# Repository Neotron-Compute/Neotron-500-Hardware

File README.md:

# Neotron 500

> A Neotron based home computer, powered by an 32-bit ARM Cortex-M7, with USB 2.0 and hardware accelerated VGA graphics.

## The top-level Specs

* 480 MHz 32-bit ARM Cortex-M7 CPU core
* 1024 KiB of fast internal ECC SRAM (used as VRAM and for OS buffers)
* 8 MiB slow external 16-bit 120 MHz SDRAM
* Super-VGA output
   * 720x400 @ 70 Hz (80x25 VGA text mode)
   * 640x480 @ 60 Hz (VGA graphics mode)
   * 800x600 @ 60 Hz (SVGA graphics mode)
   * 256 colours from a pallette of 262,144 (via 18-bit 6/6/6 DAC)
* 16-bit 48 kHz audio input and output (line-in, mic-in, line-out and headphone-out)
* Four high-speed (480 Mbps) USB 2.0 ports
   * Two USB A ports on-board
   * Header for additional two ports
* RS232 Port (five-wire)
* 2x SD/MMC Slots
* PS/2 Keyboard and Mouse ports
* Battery-backed Real-time Clock and CMOS RAM
* SPI and I²C based expansion bus

## Why 500?

We already had a Neotron 32 and a Neotron 1000, and this was somewhere inbetween the two. Plus it's roughly the performance of an Amiga 500.

## The detailed specs

### The Processor

The Neotron-500 uses an [STM32H743IIT6] microcontroller.

[STM32H743IIT6]: https://www.st.com/en/microcontrollers-microprocessors/stm32h743ii.html

```
STM32H743IIT6
vvvvv||vv|||+-- -40°C to +85°C
  |  ||| ||+-- LQFP Package
  |  ||| |+-- 2048 KiB Flash
  |  ||| +-- 176 pin
  |  ||+-- USB OTG FS/HS, Ethernet, LCD-TFT
  |  |+-- Cortex-M7
  |  +-- High-performance family
  +-- 32-bit ARM Microcontroller from ST Micro
```

This microcontroller has:

* An ARM Cortex-M7F core
  * dual-issue, six-stage pipeline
  * hardware floating point
  * 16 KiB instruction cache
  * 16 KiB data cache  
* Clockspeed of up to 480 MHz
* 176 pins, in a low-profile quad flat package (LQFP)
* 2 MiB Flash
* 128 KiB tightly-coupled (Cortex-M only) data SRAM
* 64 KiB tightly-coupled (Cortex-M only) instruction SRAM
* 512 KiB of AXI-SRAM with ECC
* Further ECC SRAM banks of 128, 128, 64 and 32 KiB each
* 4 KiB of battery-backed SRAM
* External parallel memory bus interface with SDRAM support
* Memory-mapped 133 MHz Quad-SPI interface (QSPI Flash only, not RAM)
* MII/RMII 10/100 Ethernet MAC
* USB Full-speed (12 Mbps) OTG MAC/PHY
* USB High-speed (480 Mbps) OTG MAC
* 24-bit LCD-TFT interface with ChromART 2D video accelerator
* Hardware JPEG, random number generator and CRC
* RTC with 4 KiB battery backed RAM
* MIPI CSI Camera interface
* 2x SD/MMC controllers
* Multiple I²S interfaces
* Multiple UART interfaces
* Multiple SPI bus interfaces
* Multiple I²C bus interfaces
* Multiple CAN bus interfaces

In terms of the CoreMark benchmark (and when running from internal Flash), this CPU is about the same speed as a Raspberry Pi Zero (despite running at just 40% of the clock speed), and somewhere around an 866 MHz Pentium III with 64-bit SDRAM. We run from external 16-bit SDRAM, however, and that is where we are down on performance. PC66 SDRAM is 64-bits wide and has a peak bandwidth of around 500 MiB/sec. Our 16-bit 120 MHz SDRAM meanwhile is more like 228 MiB/sec. But I'm hoping it will still run Doom.

### Memory Layout

We expect to use:

* 128 KiB tightly-coupled data SRAM for the system stack and OS data.
* 64 KiB tightly-coupled instruction SRAM for OS routines.
* 128 KiB SRAM for DMA and device buffers.
* 512 KiB AXI-SRAM for video frame buffers.
  * Highest resolution 800x600 mode @ 8bpp = 468 KiB
* (Remaining 128 KiB and 64 KiB banks TBD)
* 4 KiB battery backed SRAM for system settings
* 512 KiB internal Flash for the Neotron BIOS
* 512 KiB internal Flash for Neotron OS
* 1024 KiB internal Flash for ROM-based user applications
* 8192 KiB external SDRAM for RAM-based user applications

## The Motherboard

The Neotron 500 Motherboard is completely open-source hardware, and all the components are either through-hole parts that are easy to self install, or available from the [JLCPCB SMT assembly service].

The motherboard has:

* Regulated 5V Input
  * If you want to power four 500 mA USB devices from your Neotron 500, this needs to be capable at least 2.5A
  * TBD whether this is a DC barrel jack, full-size USB B, mini USB B or micro USB B
  * Or even take 5V from a 110V/240V internal PSU
  * Or we could take 7V-15V from a DC barrel jack and have an on-board 5V DC-DC regulator, like the Raspberry Pi CM4 IO Board
* TPS5430 3.3V 3A DC/DC Convertor (currently using an AMS1117-3.3 1A LDO)
* Winbond W9864G6KH-6 4Mx16 SDRAM
  * 8192 KiB capacity
  * 16-bit interface
  * Up to 200 MHz clock rate (we run at 120 MHz)
* Texas Instruments TLV320AIC23BPW Audio Codec ($2.32)
  * 16-bit 44.1/22.05/11.025 kHz I²S input and output to the STM32
  * Amplified stereo 3.5mm TRS headphone output
  * Line-level stereo 3.5mm TRS output
  * Line-level stereo 3.5mm TRS input
  * Mono microphone 3.5mm input
* Microchip USB3300 High-speed (480 Mbps) ULPI USB 2.0 PHY ($1.52)
* Microchip USB2514B High-speed (480 Mbps) four port USB 2.0 hub, with 2x2 USB 2.0 A ports. ($1.43)
* 18-bit (6-6-6) R2R DAC and 3PEAK TPF133A HD video output buffer ($0.16), with standard DE15HD VGA connector.
* Maybe a TPD7S019 ESD protection device / SYNC buffer for the VGA connector ($0.26)
* Full-size external-facing SD Card slot (drive A:)
* Full-size internal SD Card slot (drive C:)
* Maxim MAX16054 on-off controller ($1.11)
* Keyboard / Mouse interface
  * 2x PS/2 Ports for keyboard and mouse (2x mini-DIN 6-pin sockets)
* Power switch and reset switch
* RS232 Port (five-wire, 10-pin IDC box header as used on PCs)
* Coin-cell for the STM32's real-time clock and battery-backed SRAM
* SPI/QSPI and I²C based expansion bus
  * There are seven slots
  * Each slot has a unique SPI Chip-select and IRQ line
  * Each slot contains a unique 3-bit value, which is routed to the 3 address pins of an M24C02 256 byte I²C EEPROM on the expansion card
  * The I²C EEPROM describes that expansion card (similar to the Raspberry Pi HAT specification, but supporting multiple slots)

[JLCPCB SMT assembly service]: https://jlcpcb.com/parts

Expected price is $40 for the motherboard with SMT parts loaded, and another $20 for the through-hole connectors. The system does not include a Parallel Port, Ethernet, Joystick ports, Keyboard matrix controller, MIDI ports or Wi-Fi - modules can be added via the SPI expansion ports for these features. Although the STM32F7 does have an on-board Ethernet MAC, we cannot use it and all the other interfaces (SDRAM, SDMMC, ULPI, LCD) at the same time.

## Software

This system is designed to run the Neotron OS. To do that, it has a bespoke version of the Neotron BIOS. It is compatible with all 'well-behaved' Neotron applications that stick to the Neotron OS APIs rather than poking hardware directly.

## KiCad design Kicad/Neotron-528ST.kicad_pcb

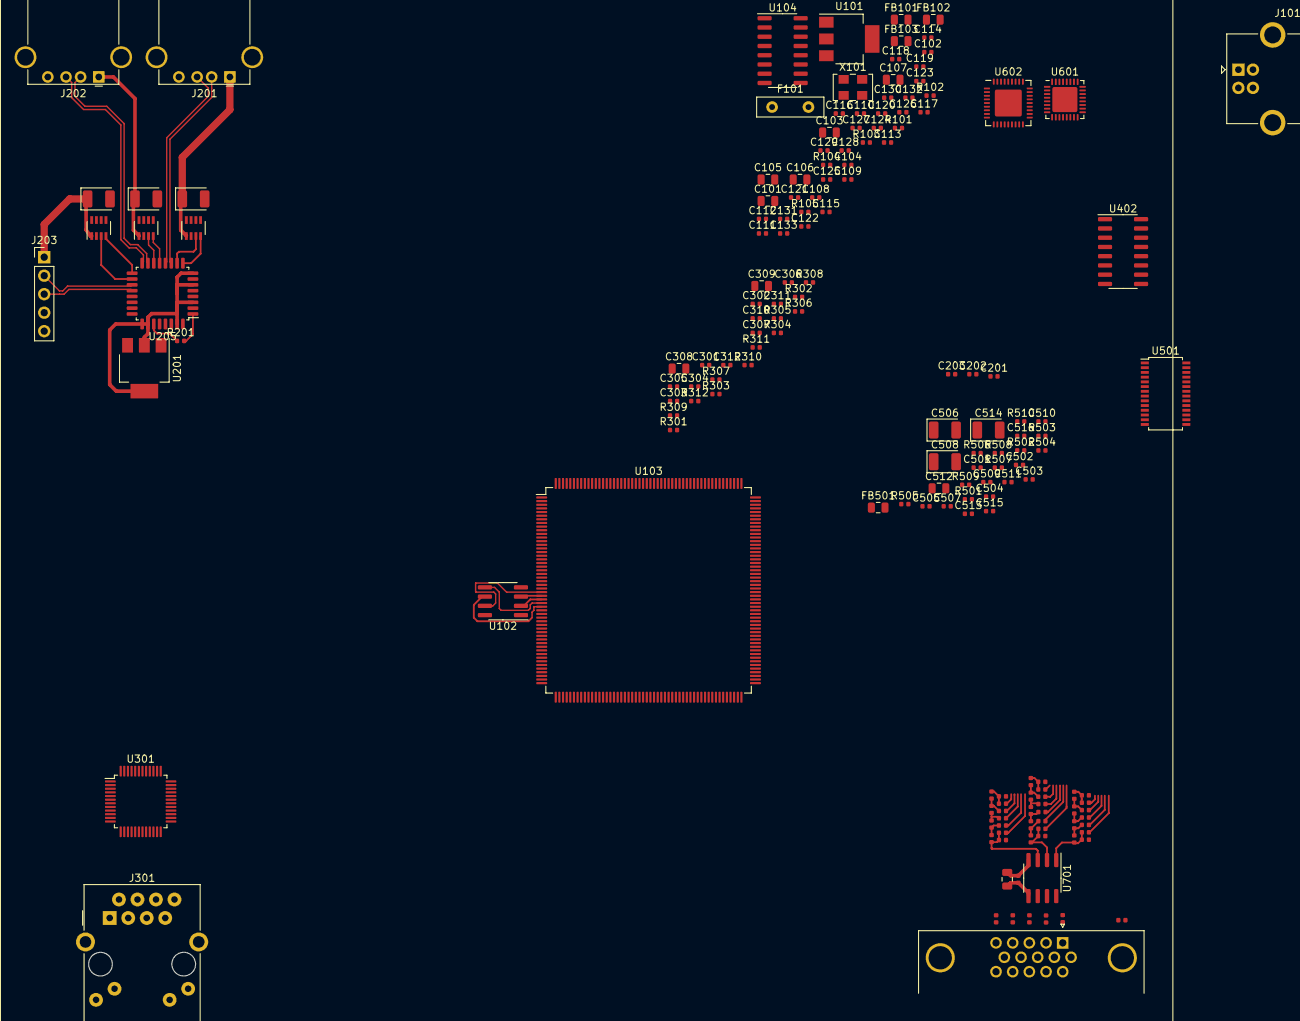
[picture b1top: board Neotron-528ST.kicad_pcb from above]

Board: 2 copper layers, 165 parts (0 on the bottom side), 125 nets.

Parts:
C101, C103, C105: 22u; C_0805_2012Metric
C102, C104, C108, C113, C115, C117, C119, C120, C121, C122, C123, C124, C125, C126, C128, C129, C130, C131, C132, C133, C201, C301, C302, C303, C304, C305, C306, C307, C310, C311, C312, C511, C513, C702: 100n; C_0402_1005Metric
C106, C107: 2.2u; C_0805_2012Metric
C109, C110, C111, C112: 9p; C_0402_1005Metric
C114, C116, C118, C127, C501, C502, C504, C505, C509: 1u; C_0402_1005Metric
C202, C203: 4.7u; C_0402_1005Metric
C204, C205, C206, C506, C508, C514: 100u; CP_EIA-3528-21_Kemet-B
C308, C309, C512: 10u; C_0805_2012Metric
C503, C507, C510: 47p; C_0402_1005Metric
C515, C516: 27p; C_0402_1005Metric
C701: 4.7u; C_0805_2012Metric
F101: 2.5A; C_Disc_D9.0mm_W2.5mm_P5.00mm
FB101, FB102, FB103, FB501: 100R@100MHz; L_0805_2012Metric
J101: USB_B; USB_B_OST_USB-B1HSxx_Horizontal
J201, J202: USB_A; USB_A_Stewart_SS-52100-001_Horizontal
J203: USB_A; PinHeader_1x05_P2.54mm_Vertical
J301: RJ45_Amphenol_RJMG1BD3B8K1ANR
J701: DB15_Female_HighDensity_MountingHoles; DSUB-15-HD_Female_Horizontal_P2.29x1.98mm_EdgePinOffset3.03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
R101, R102, R103, R312: 0R; R_0402_1005Metric
R104, R105: 10k; R_0402_1005Metric
R201: 1.5k; R_0402_1005Metric
R301, R302, R305, R307: 49.9R; R_0402_1005Metric
R303, R304, R306, R310: 2k2; R_0402_1005Metric
R308, R309: 1k; R_0402_1005Metric
R311: 4.87K; R_0402_1005Metric
R501: 2.2k; R_0402_1005Metric
R502, R503, R506, R507: 100k; R_0402_1005Metric
R504, R508: 4.99k; R_0402_1005Metric
R505, R509: 5k; R_0402_1005Metric
R510: 3R3; R_0402_1005Metric
R701, R702, R703, R704, R705, R711, R717, R718, R719, R720, R721, R722, R729, R731, R732, R733, R734, R735, R740: 24K; R_0402_1005Metric
R706, R707, R708, R709, R724, R725, R726, R727, R728, R736, R737, R738, R739: 12K; R_0402_1005Metric
R710, R730, R741: 3K3; R_0402_1005Metric
R712, R713, R714: 75; R_0402_1005Metric
R715, R716: 470; R_0402_1005Metric
R723: 0; R_0402_1005Metric
U101, U201: AMS1117-3.3; SOT-223-3_TabPin2
U102: LY68S3200SLT; SOIC-8_3.9x4.9mm_P1.27mm
U103: STM32F767BGTx; LQFP-208_28x28mm_P0.5mm
U104: MAX232; SOIC-16_3.9x9.9mm_P1.27mm
U202, U203, U204: AAT4610BIGV-1-T1; SOT-23-8
U205: TUSB2036; LQFP-32_7x7mm_P0.8mm
U301: DP83848C; LQFP-48_7x7mm_P0.5mm
U402: 74LS138; SOIC-16_3.9x9.9mm_P1.27mm
U501: TLV320AIC23BPW; TSSOP-28_4.4x9.7mm_P0.65mm
U601: USB3300-EZK; QFN-32-1EP_5x5mm_P0.5mm_EP3.45x3.45mm
U602: USB2514B_Bi; QFN-36-1EP_6x6mm_P0.5mm_EP3.7x3.7mm
U701: TPF133A; SOIC-8_3.9x4.9mm_P1.27mm
X101: 50MHz XO; Oscillator_SMD_TXC_7C-4Pin_5.0x3.2mm

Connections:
+3V3: C108.1, C301.1, C302.1, C303.1, C304.1, C511.1, C512.1, C701.1, C702.1, FB501.1, J301.R4, J301.R5, R301.2, R302.1, R305.2, R306.1, R307.1, R308.2, R309.2, R310.1, R312.2, U102.8, U301.22, U301.32, U301.48, U501.1, U501.22, U501.27, U701.4, X101.1, X101.4
+5V: C101.1, C104.1, C105.1, C201.1, C202.1, F101.1, U101.3, U201.3, U202.5, U203.5, U204.5
/Audio/HEADPHONE_L: C506.1, U501.9
/Audio/HEADPHONE_R: C508.1, U501.10
/Audio/LINE_IN_L: C505.1, U501.20
/Audio/LINE_IN_R: C509.1, U501.19
/Audio/LINE_OUT_L: C502.1, U501.12
/Audio/LINE_OUT_R: C504.1, U501.13
/Audio/MIC_IN: C501.1, U501.18
/Audio/VDD_AUDIO: C513.1, C514.1, FB501.2, R510.2, U501.8
/Audio/V_MICBIAS: R501.1, U501.17
/Ethernet PHY/LED_ACT: J301.L2, U301.26
/Ethernet PHY/LED_SPEED: J301.L3, U301.27
/LTDC_B3: R731.1, U103.110
/LTDC_B4: R732.1, U103.144
/LTDC_B5: R733.1, U103.187
/LTDC_B6: R734.1, U103.188
/LTDC_B7: R735.1, U103.189
/LTDC_G2: R717.1, U103.55
/LTDC_G3: R718.1, U103.85
/LTDC_G4: R719.1, U103.123
/LTDC_G5: R720.1, U103.126
/LTDC_G6: R721.1, U103.127
/LTDC_G7: R722.1, U103.128
/LTDC_HSYNC: R715.2, U103.12
/LTDC_R3: R701.1, U103.67
/LTDC_R4: R702.1, U103.68
/LTDC_R5: R703.1, U103.69
/LTDC_R6: R704.1, U103.95
/LTDC_R7: R705.1, U103.65
/LTDC_VSYNC: R716.2, U103.11
/QUADSPI_BK1_IO0: U102.2, U103.29
/QUADSPI_BK1_IO1: U102.5, U103.30
/QUADSPI_BK1_IO2: U102.3, U103.28
/QUADSPI_BK1_IO3: U102.7, U103.27
/QUADSPI_BK1_NCS: U102.1, U103.195
/QUADSPI_CLK: U102.6, U103.31
/RCC_OSC32_IN: C111.1, U103.9
/RCC_OSC32_OUT: C112.1, U103.10
/RCC_OSC_IN: C109.1, U103.32
/RCC_OSC_OUT: C110.1, U103.33
/USB 1.1 Host/HUB_3V3: C203.1, U201.2, U205.3, U205.6, U205.8, U205.25, U205.26, U205.31
/USB 1.1 Host/PORT1_D+: J201.3, U205.12
/USB 1.1 Host/PORT1_D-: J201.2, U205.11
/USB 1.1 Host/PORT2_D+: J202.3, U205.16
/USB 1.1 Host/PORT2_D-: J202.2, U205.15
/USB 1.1 Host/PORT3_D+: J203.3, U205.20
/USB 1.1 Host/PORT3_D-: J203.2, U205.19
/USB 1.1 Host/~PORT1_EN: U202.4, U205.9
/USB 1.1 Host/~PORT1_OC: U202.3, U205.10
/USB 1.1 Host/~PORT2_EN: U203.4, U205.13
/USB 1.1 Host/~PORT2_OC: U203.3, U205.14
/USB 1.1 Host/~PORT3_EN: U204.4, U205.17
/USB 1.1 Host/~PORT3_OC: U204.3, U205.18
/USB_OTG_HS_D+: R201.2, U205.1
/VDDA: C115.1, C116.1, FB101.2, R101.2, U103.42
/VDD_MCU: C102.1, C103.1, C119.1, C120.1, C121.1, C122.1, C123.1, C124.1, C125.1, C128.1, C129.1, C130.1, C131.1, C132.1, C133.1, FB101.1, R102.2, R103.2, U101.2, U103.15, U103.26, U103.39, U103.52, U103.59, U103.73, U103.83, U103.94, U103.103, U103.115, U103.124, U103.150, U103.158, U103.185, U103.204
/VDD_SDMMC: C126.1, C127.1, R102.1, U103.171
/VDD_USB: C117.1, C118.1, R103.1, U103.137
/VGA Video Output/ANALOG_BLUE: R735.2, R739.1, R741.1, U701.3
/VGA Video Output/ANALOG_GREEN: R722.2, R728.1, R730.1, U701.2
/VGA Video Output/ANALOG_RED: R705.2, R709.1, R710.1, U701.1
/VGA Video Output/BOUT: R714.1, U701.6
/VGA Video Output/GOUT: R713.1, U701.7
/VGA Video Output/ROUT: R712.1, U701.8
/VREF+: C113.1, C114.1, R101.1, U103.41
GND: C101.2, C102.2, C103.2, C104.2, C105.2, C106.2, C107.2, C108.2, C109.2, C110.2, C111.2, C112.2, C113.2, C114.2, C115.2, C116.2, C117.2, C118.2, C119.2, C120.2, C121.2, C122.2, C123.2, C124.2, C125.2, C126.2, C127.2, C128.2, C129.2, C130.2, C131.2, C132.2, C133.2, C201.2, C202.2, C203.2, C204.2, C205.2, C206.2, C301.2, C302.2, C303.2, C304.2, C305.2, C306.2, C307.2, C308.2, C309.2, C310.2, C311.2, C312.2, C511.2, C512.2, C513.2, C514.2, C515.2, C516.2, C701.2, C702.2, FB103.1, J101.4, J201.4, J201.5, J202.4, J202.5, J203.4, J203.5, J301.13, J301.R8, J701.5, J701.6, J701.7, J701.8, R104.2, R303.2, R304.2, R311.1, R710.2, R711.2, R723.2, R729.2, R730.2, R740.2, R741.2, U101.1, U102.4, U103.14, U103.25, U103.40, U103.51, U103.60, U103.72, U103.82, U103.93, U103.114, U103.125, U103.136, U103.149, U103.170, U103.184, U103.202, U201.1, U202.2, U203.2, U204.2, U205.7, U205.21, U205.22, U205.23, U205.24, U205.28, U301.15, U301.19, U301.35, U301.36, U301.47, U501.28, U701.5, X101.2
GNDA: C503.2, C507.2, C510.2, R502.1, R503.1, R505.1, R506.1, R507.1, R509.1, U501.11, U501.15
unnamed: C106.1, U103.92
unnamed: C107.1, U103.148
unnamed: C204.1, J201.1, U202.1
unnamed: C205.1, J202.1, U203.1
unnamed: C206.1, J203.1, U204.1
unnamed: C305.1, U301.37
unnamed: C306.1, U301.18
unnamed: C307.1, C308.1, U301.23
unnamed: C309.1, C310.1, C311.1, C312.1, R312.1
unnamed: C501.2, C503.1, R501.2
unnamed: C502.2, R502.2
unnamed: C504.2, R503.2
unnamed: C505.2, C507.1, R504.1, R505.2
unnamed: C506.2, R506.2
unnamed: C508.2, R507.2
unnamed: C509.2, C510.1, R508.1, R509.2
unnamed: C515.1, U501.25
unnamed: C516.1, U501.26
unnamed: F101.2, FB102.2
unnamed: FB102.1, J101.1
unnamed: FB103.2, J101.5
unnamed: J301.L1, R309.1
unnamed: J301.L4, R308.1
unnamed: J301.R1, R301.1, U301.17
unnamed: J301.R2, R302.2, U301.16
unnamed: J301.R3, R305.1, U301.14
unnamed: J301.R6, R307.2, U301.13
unnamed: J701.0, R723.1
unnamed: J701.1, R712.2
unnamed: J701.2, R713.2
unnamed: J701.3, R714.2
unnamed: J701.13, R715.1
unnamed: J701.14, R716.1
unnamed: R104.1, U103.203
unnamed: R105.1, U103.197
unnamed: R201.1, U205.27
unnamed: R303.1, U301.5
unnamed: R304.1, U301.6
unnamed: R306.2, U301.39
unnamed: R310.2, U301.7
unnamed: R311.2, U301.24
unnamed: R510.1, U501.14
unnamed: R701.2, R706.2, R711.1
unnamed: R702.2, R706.1, R707.2
unnamed: R703.2, R707.1, R708.2
unnamed: R704.2, R708.1, R709.2
unnamed: R717.2, R724.2, R729.1
unnamed: R718.2, R724.1, R725.2
unnamed: R719.2, R725.1, R726.2
unnamed: R720.2, R726.1, R727.2
unnamed: R721.2, R727.1, R728.2
unnamed: R731.2, R736.2, R740.1
unnamed: R732.2, R736.1, R737.2
unnamed: R733.2, R737.1, R738.2
unnamed: R734.2, R738.1, R739.2
unnamed: U601.7, U602.31
unnamed: U601.8, U602.30

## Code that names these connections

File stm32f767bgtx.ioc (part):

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PK5.Signal=LTDC_B6
PH12.Signal=I2C4_SDA
PB10.Mode=Host_HS
PK0.Mode=RGB565
PG4.Signal=FMC_A14_BA0
PC12.Signal=SDMMC1_CK
PG0.Signal=FMC_A10
PC5.Mode=MII
PK1.Signal=LTDC_G6
PB13.Signal=USB_OTG_HS_ULPI_D6
PG13.Signal=ETH_TXD0
PA4.Mode=Half_Duplex_Slave
PF7.Signal=QUADSPI_BK1_IO2
PJ5.Mode=RGB565
PD4.Signal=FMC_NOE
PB6.Signal=QUADSPI_BK1_NCS
PC7.Signal=FMC_NE1
PH1/OSC_OUT.Signal=RCC_OSC_OUT
PB6.Mode=Single Bank 1
PC3.Signal=ETH_TX_CLK
PD0.Signal=FMC_D2_DA2
PD8.Signal=USART3_TX
PE5.Signal=FMC_A21
PI3.Mode=Half_Duplex_Master
PB2.Signal=I2S3_SD
PB3.Mode=Half_Duplex_Slave
PG14.Mode=MII
PK7.Mode=RGB565
PJ2.Mode=RGB565
PE9.Signal=FMC_D6_DA6
PB14.Mode=CTS_RTS
PI3.Signal=I2S2_SD
PC9.Mode=SD_4_bits_Wide_bus
PE2.Signal=FMC_A23
PF8.Mode=Single Bank 1
PA8.Signal=RCC_MCO_1
PE13.Mode=Full_Duplex_Master
PF3.Signal=FMC_A3
PE10.Signal=FMC_D7_DA7
Mcu.Package=LQFP208
PB1.Signal=USB_OTG_HS_ULPI_D2
PH12.Mode=I2C
PD12.Signal=FMC_A17_ALE
PH11.Mode=I2C
PJ4.Signal=LTDC_R5
PA10.Signal=LTDC_B4
PC11.Mode=SD_4_bits_Wide_bus
PF14.Signal=FMC_A8
PF10.Mode=Single Bank 1
PB13.Mode=Host_HS
PI11.Signal=USB_OTG_HS_ULPI_DIR
PD15.Signal=FMC_D1_DA1
PC4.Mode=MII
PA5.Mode=Host_HS
PE12.Mode=Full_Duplex_Master
PK4.Signal=LTDC_B5
PG5.Signal=FMC_A15_BA1
PI10.Mode=RGB565
PC6.Signal=I2S2_MCK
PC2.Signal=ETH_TXD2
PD1.Signal=FMC_D3_DA3
PC0.Signal=USB_OTG_HS_ULPI_STP
PJ11.Signal=LTDC_G4
PD10.Signal=LTDC_B3
PA3.Mode=Host_HS
PJ3.Signal=LTDC_R4
PB11.Mode=Host_HS
PC6.Mode=Master_Clock_Activated
PA9.Signal=I2S2_CK
PD8.Mode=Asynchronous
PA0/WKUP.Mode=MII
PB10.Signal=USB_OTG_HS_ULPI_D3
PB14.Signal=UART4_RTS
PA5.Signal=USB_OTG_HS_ULPI_CK
PC12.Mode=SD_4_bits_Wide_bus
PH6.Mode=MII
PA1.Mode=MII
PE14.Signal=SPI4_MOSI
PE8.Signal=FMC_D5_DA5
PF13.Signal=FMC_A7
PH4.Mode=Host_HS
PC8.Mode=SD_4_bits_Wide_bus
PA4.Signal=I2S3_WS
PB5.Signal=USB_OTG_HS_ULPI_D7
PK4.Mode=RGB565
PD11.Signal=FMC_A16_CLE
PG11.Mode=MII
PA11.Signal=UART4_RX
PB1.Mode=Host_HS
PH6.Signal=ETH_RXD2
PF6.Mode=Single Bank 1
PF9.Signal=QUADSPI_BK1_IO1
PB8.Mode=MII
PE3.Signal=FMC_A19
PJ4.Mode=RGB565
PC15/OSC32_OUT.Signal=RCC_OSC32_OUT
PA8.Mode=Clock-out-1
PF4.Signal=FMC_A4
PD2.Signal=SDMMC1_CMD
PB0.Signal=USB_OTG_HS_ULPI_D1
PC1.Signal=ETH_MDC
PC1.Mode=MII
PC3.Mode=MII
PK7.Signal=LTDC_DE
PA6.Mode=RGB565
Mcu.UserName=STM32F767BGTx
PG2.Signal=FMC_A12
PC10.Signal=SDMMC1_D2
PA11.Mode=Asynchronous
PA0/WKUP.Signal=ETH_CRS
PC14/OSC32_IN.Mode=LSE-External-Oscillator
PB11.Signal=USB_OTG_HS_ULPI_D4
PB15.Signal=UART4_CTS
PD9.Mode=Asynchronous
PG11.Signal=ETH_TX_EN
PH3.Mode=MII
PD13.Signal=FMC_A18
PI11.Mode=Host_HS
PA12.Signal=UART4_TX
PJ2.Signal=LTDC_R3
PE11.Mode=RGB565
PH0/OSC_IN.Mode=HSE-External-Oscillator
PF12.Signal=FMC_A6
PI9.Mode=RGB565
PD10.Mode=RGB565
PK2.Mode=RGB565
RCC.HSE_VALUE=25000000
PI14.Mode=RGB565
PF9.Mode=Single Bank 1
PE13.Signal=SPI4_MISO
PK6.Mode=RGB565
PI0.Signal=I2S2_WS
PB5.Mode=Host_HS
PG13.Mode=MII
PH1/OSC_OUT.Mode=HSE-External-Oscillator
PE4.Signal=FMC_A20
PH7.Mode=MII
PJ0.Mode=RGB565
PA6.Signal=LTDC_G2
PB12.Mode=Host_HS
PC14/OSC32_IN.Signal=RCC_OSC32_IN
PF8.Signal=QUADSPI_BK1_IO0
PF5.Signal=FMC_A5
PH7.Signal=ETH_RXD3
PF0.Signal=FMC_A0
PC5.Signal=ETH_RXD1
PE7.Signal=FMC_D4_DA4
PD6.Signal=FMC_NWAIT
PA3.Signal=USB_OTG_HS_ULPI_D0
PK1.Mode=RGB565
PK6.Signal=LTDC_B7
PK2.Signal=LTDC_G7
PA7.Mode=MII
PA10.Mode=RGB565
PH11.Signal=I2C4_SCL
PG3.Signal=FMC_A13
PG1.Signal=FMC_A11
PC11.Signal=SDMMC1_D3
PI14.Signal=LTDC_CLK
PC8.Signal=SDMMC1_D0
PC4.Signal=ETH_RXD0
PC10.Mode=SD_4_bits_Wide_bus
PC2.Mode=MII
PI10.Signal=LTDC_HSYNC
PD9.Signal=USART3_RX
PD5.Signal=FMC_NWE
PC0.Mode=Host_HS
PJ11.Mode=RGB565
PF7.Mode=Single Bank 1
PA9.Mode=Half_Duplex_Master
PH4.Signal=USB_OTG_HS_ULPI_NXT
PF6.Signal=QUADSPI_BK1_IO3
PI0.Mode=Half_Duplex_Master
PF2.Signal=FMC_A2
PE11.Signal=LTDC_G3
PA1.Signal=ETH_RX_CLK
PK0.Signal=LTDC_G5
PD2.Mode=SD_4_bits_Wide_bus
PK5.Mode=RGB565
PG14.Signal=ETH_TXD1
PB0.Mode=Host_HS
board=custom
PI9.Signal=LTDC_VSYNC
PB15.Mode=CTS_RTS
PJ3.Mode=RGB565
PH0/OSC_IN.Signal=RCC_OSC_IN
PF10.Signal=QUADSPI_CLK
PE14.Mode=Full_Duplex_Master
PF15.Signal=FMC_A9
PF1.Signal=FMC_A1
PE6.Signal=FMC_A22
PJ0.Signal=LTDC_R7
Mcu.Name=STM32F767B(G-I)Tx
PE12.Signal=SPI4_SCK
PA2.Signal=ETH_MDIO
PD14.Signal=FMC_D0_DA0
PB3.Signal=I2S3_CK
PA12.Mode=Asynchronous
PB2.Mode=Half_Duplex_Slave
PC15/OSC32_OUT.Mode=LSE-External-Oscillator
PJ5.Signal=LTDC_R6
PH3.Signal=ETH_COL
PA2.Mode=MII
PB8.Signal=ETH_TXD3
PC9.Signal=SDMMC1_D1
PC7.Mode=NorPsramChipSelect1_1
PB12.Signal=USB_OTG_HS_ULPI_D5
PA7.Signal=ETH_RX_DV

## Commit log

2020-05-30 First pass with 208 pin chip.
2020-05-30 Move IOC file
2020-05-30 Rename kicad folder
2020-06-01 Swap Flash for ESP-PSRAM as it's closer to the part we actually want.
2020-06-05 Work in progress
2020-06-09 Adding VGA output buffer/filter.
2020-06-09 Adding README
2020-06-09 Adding project-specific library of parts.
2020-06-09 Adding datasheets
2020-06-09 Update README.
2020-06-13 Renamed to Neotron-528ST
2020-06-15 Removed USB FS hub. Added stacked USB A connector.
2020-06-17 Update the README
2020-06-28 Switched over to H7
2020-06-28 Renamed KiCad files.
2020-06-28 Swap to H7 in the Schematic
2020-06-28 README tweaks.
    Added more RAM performance details.
2020-10-20 Collecting random thoughts
2020-10-20 Schematic updates
    Worked on USB Hub
    Deleted QSPI SRAM
    Added TSSOP-54 SDRAM (not wired up)
2020-10-31 Added more details after some research.
2020-11-15 Tidying up schematic, and README.
